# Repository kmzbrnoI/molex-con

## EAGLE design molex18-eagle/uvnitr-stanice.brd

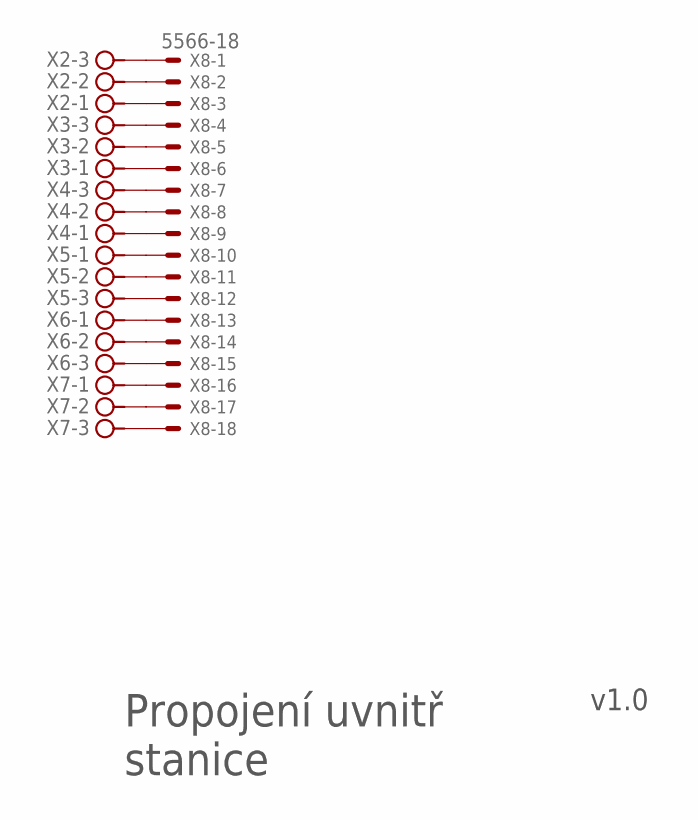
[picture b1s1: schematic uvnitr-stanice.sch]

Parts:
X2, X3, X4, X5, X6, X7: ARK500/3
X8: 5566-18

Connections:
unnamed: X2.1, X8.3
unnamed: X2.2, X8.2
unnamed: X2.3, X8.1
unnamed: X3.1, X8.6
unnamed: X3.2, X8.5
unnamed: X3.3, X8.4
unnamed: X4.1, X8.9
unnamed: X4.2, X8.8
unnamed: X4.3, X8.7
unnamed: X5.1, X8.10
unnamed: X5.2, X8.11
unnamed: X5.3, X8.12
unnamed: X6.1, X8.13
unnamed: X6.2, X8.14
unnamed: X6.3, X8.15
unnamed: X7.1, X8.16
unnamed: X7.2, X8.17
unnamed: X7.3, X8.18

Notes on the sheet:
Propojení uvnitř stanice
v1.0

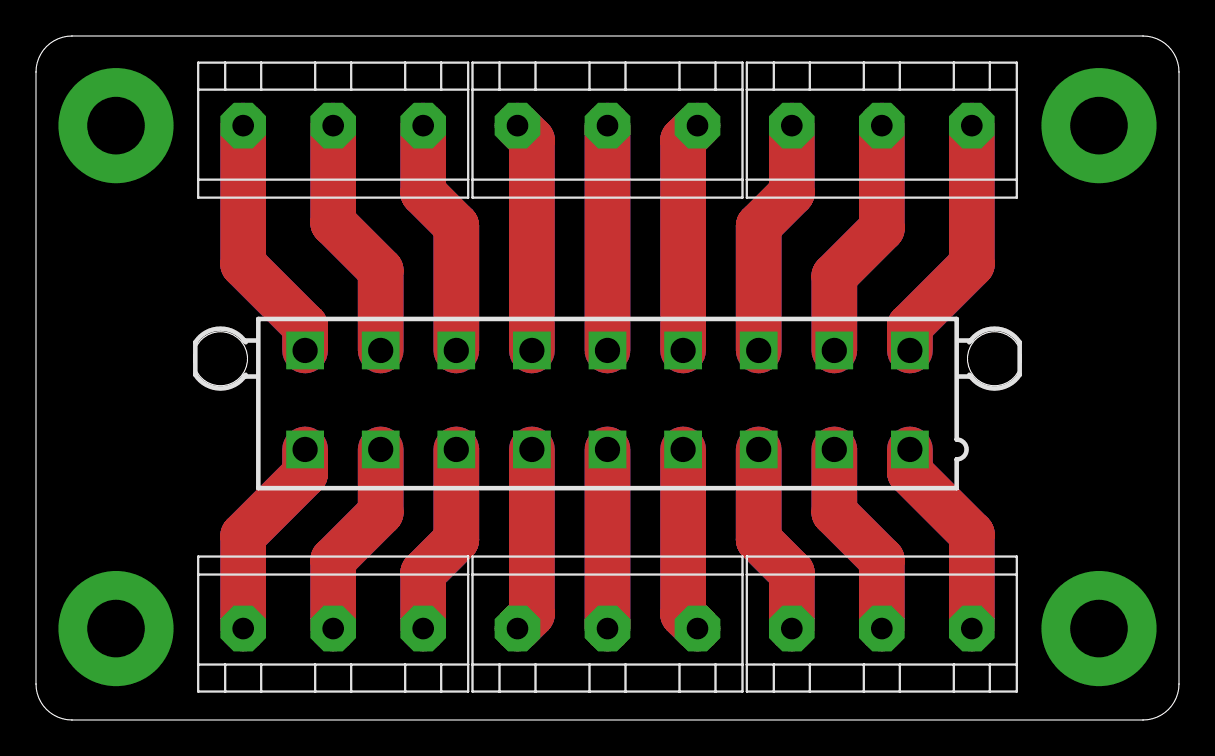
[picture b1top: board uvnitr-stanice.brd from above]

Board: 2 copper layers, 63.5 x 38.0 mm, 7 parts (0 on the bottom side), 18 nets.

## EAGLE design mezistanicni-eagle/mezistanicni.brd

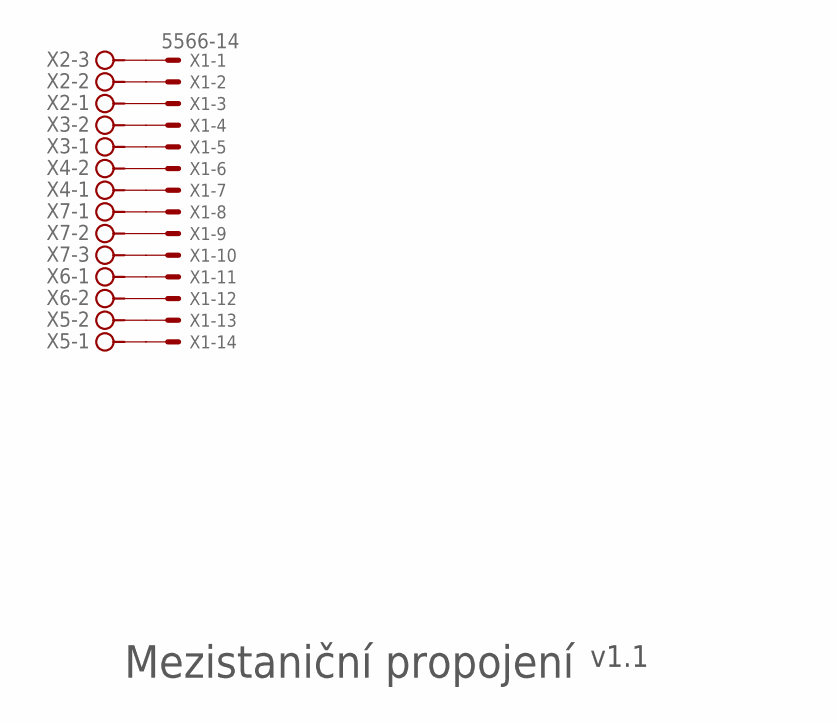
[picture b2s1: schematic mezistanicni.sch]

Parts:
X1: 5566-14
X2, X7: MVE253-5-V
X3, X6: MVE252-5-V
X4, X5: ARK550/2

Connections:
B-AC+: X1.9, X7.2
B-AC-GND: X1.8, X7.1
DCC-C: X1.14, X5.1
DCC-D: X1.13, X5.2
GND: X1.1, X2.3
MTB: X1.2, X2.2
MTBBUS+: X1.7, X4.1
MTBBUS-: X1.6, X4.2
NC1: X1.12, X6.2
NC2: X1.11, X6.1
NC3: X1.10, X7.3
POM: X1.3, X2.1
PREST: X1.5, X3.1
ROZP: X1.4, X3.2

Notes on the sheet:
Mezistaniční propojení
v1.1

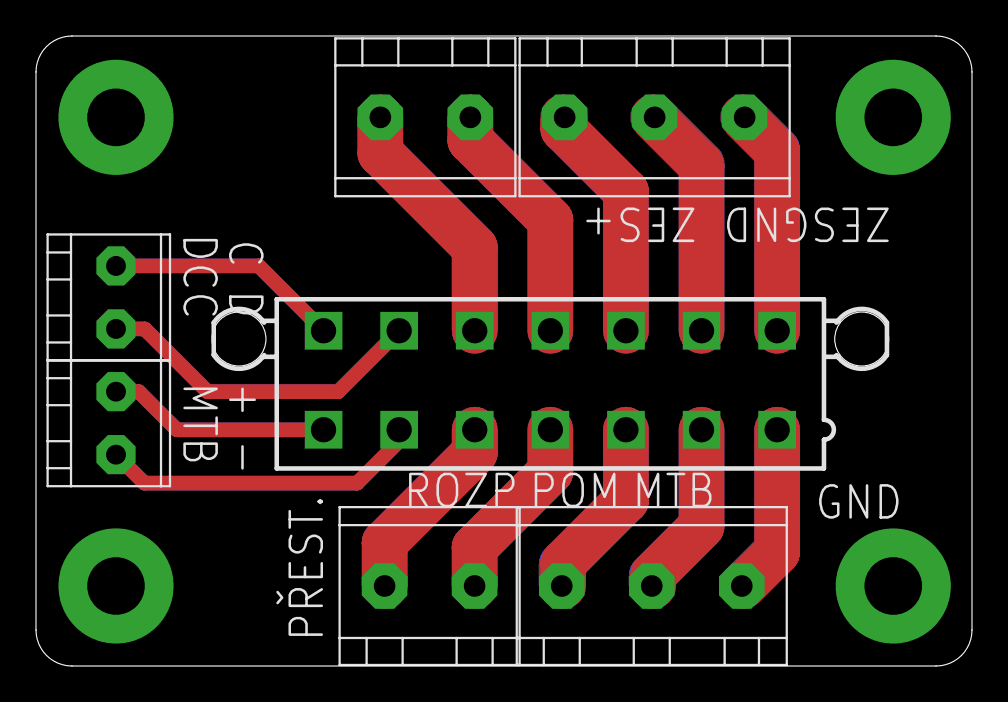
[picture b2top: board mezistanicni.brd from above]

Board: 2 copper layers, 52.0 x 35.0 mm, 7 parts (0 on the bottom side), 14 nets.

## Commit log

2022-12-02 Add KiCad .gitignore.
2022-12-02 Add empty KiCad project.
2022-12-02 Draw schematics, route pcb.
2022-12-02 Add makefile.
2022-12-31 Move molex8 to 'molex8' subdirectory.
2022-12-31 Customize modulovka pcb.
2022-12-31 Modulovka: makefile.
2022-12-31 Add generated files to .gitignore.
2022-12-31 molex8: fix akefile.
2022-12-31 Update silkscreen.
2023-02-15 Standardize dimensions to 42x42 mm.
2024-06-13 Add molex14 & molex18 PCBs.
2024-06-14 Add molex10-zdroj.
2024-06-15 Use screw terminal symbols, use MVE25-5-V as values.
2024-06-20 Add molex10-stanice.
2024-06-20 Do not panelize molex10-zdroj.
2024-06-25 molex10-zdroj: flip MOLEX to bottom side.
2024-06-25 molex10-stanice: slight enhancements.
2024-06-25 molex10-stanice: remove solder mask on wires.
2024-06-25 molex10: Use blue solder mask.
2024-06-25 Add note regarding PYTHONPATH.
2025-02-15 molex10-zdroj: center MOLEX connector horizontally.
    PCB v1.1
2025-04-01 molex10-zdroj: update to KiCad 9, add silkscreen desc.
2025-05-13 modulovka: migrate to KiCad 9.
2025-05-13 modulovka: name wires, fix conn symbol, fix switched 2-3.
2025-05-13 molex8: migrate to KiCad 9.
2025-05-13 molex8: add wire names.
